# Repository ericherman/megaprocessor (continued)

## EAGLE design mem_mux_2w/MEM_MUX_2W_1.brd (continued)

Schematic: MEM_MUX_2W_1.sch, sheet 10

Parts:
Q61, Q62, Q63, Q64, Q65, Q66, Q67, Q68, Q69, Q70, Q71, Q72, Q73, Q74, Q75, Q76, Q77, Q78, Q79, Q80, Q81, Q82, Q83, Q84: 2N7000; TO92-DGS
R77, R78, R79, R80, R81, R82, R83, R84, R85, R86, R87, R88, R89, R90, R91, R92, R93, R94, R95, R96, R97, R98, R99, R100: 10k; R_P2INCH

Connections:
+5V: R77.2, R78.2, R79.2, R80.2, R81.2, R82.2, R83.2, R84.2, R85.2, R86.2, R87.2, R88.2, R89.2, R90.2, R91.2, R92.2, R93.2, R94.2, R95.2, R96.2, R97.2, R98.2, R99.2, R100.2; also elsewhere on the board
A0_N: Q69.G; also elsewhere on the board
A1_N: Q70.G; also elsewhere on the board
A2_N: Q71.G; also elsewhere on the board
A3_N: Q72.G; also elsewhere on the board
A4_N: Q73.G; also elsewhere on the board
A5_N: Q74.G; also elsewhere on the board
A6_N: Q75.G; also elsewhere on the board
A7_N: Q76.G; also elsewhere on the board
A8_N: Q77.G; also elsewhere on the board
A9_N: Q78.G; also elsewhere on the board
A10_N: Q79.G; also elsewhere on the board
A11_N: Q80.G; also elsewhere on the board
A12_N: Q81.G; also elsewhere on the board
A13_N: Q82.G; also elsewhere on the board
A14_N: Q83.G; also elsewhere on the board
A15_N: Q84.G; also elsewhere on the board
GND: Q61.S, Q62.S, Q63.S, Q64.S, Q65.S, Q66.S, Q67.S, Q68.S, Q69.S, Q70.S, Q71.S, Q72.S, Q73.S, Q74.S, Q75.S, Q76.S, Q77.S, Q78.S, Q79.S, Q80.S, Q81.S, Q82.S, Q83.S, Q84.S; also elsewhere on the board
P1_A0: Q69.D, R85.1; also elsewhere on the board
P1_A1: Q70.D, R86.1; also elsewhere on the board
P1_A2: Q71.D, R87.1; also elsewhere on the board
P1_A3: Q72.D, R88.1; also elsewhere on the board
P1_A4: Q73.D, R89.1; also elsewhere on the board
P1_A5: Q74.D, R90.1; also elsewhere on the board
P1_A6: Q75.D, R91.1; also elsewhere on the board
P1_A7: Q76.D, R92.1; also elsewhere on the board
P1_A8: Q77.D, R93.1; also elsewhere on the board
P1_A9: Q78.D, R94.1; also elsewhere on the board
P1_A10: Q79.D, R95.1; also elsewhere on the board
P1_A11: Q80.D, R96.1; also elsewhere on the board
P1_A12: Q81.D, R97.1; also elsewhere on the board
P1_A13: Q82.D, R98.1; also elsewhere on the board
P1_A14: Q83.D, R99.1; also elsewhere on the board
P1_A15: Q84.D, R100.1; also elsewhere on the board
P1_WD0: Q61.D, R77.1; also elsewhere on the board
P1_WD1: Q62.D, R78.1; also elsewhere on the board
P1_WD2: Q63.D, R79.1; also elsewhere on the board
P1_WD3: Q64.D, R80.1; also elsewhere on the board
P1_WD4: Q65.D, R81.1; also elsewhere on the board
P1_WD5: Q66.D, R82.1; also elsewhere on the board
P1_WD6: Q67.D, R83.1; also elsewhere on the board
P1_WD7: Q68.D, R84.1; also elsewhere on the board
WD0_N: Q61.G; also elsewhere on the board
WD1_N: Q62.G; also elsewhere on the board
WD2_N: Q63.G; also elsewhere on the board
WD3_N: Q64.G; also elsewhere on the board
WD4_N: Q65.G; also elsewhere on the board
WD5_N: Q66.G; also elsewhere on the board
WD6_N: Q67.G; also elsewhere on the board
WD7_N: Q68.G; also elsewhere on the board

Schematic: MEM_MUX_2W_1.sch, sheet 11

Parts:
D33, D34, D35, D69: L-1334SRT; LED3MM
Q169, Q170, Q171, Q174, Q175, Q176, Q179, Q180, Q181, Q184, Q185, Q186: 2N7000; TO92-DGS
R201, R203, R205, R207, R257, R258, R259, R260: 10k; R_P2INCH
R202, R204, R206, R208: 470; R_P2INCH

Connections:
+5V: D33.A, D34.A, D35.A, D69.A, R201.2, R203.2, R205.2, R207.2, R257.2, R258.2, R259.2, R260.2; also elsewhere on the board
GND: Q170.S, Q171.S, Q175.S, Q176.S, Q180.S, Q181.S, Q185.S, Q186.S; also elsewhere on the board
unnamed: Q174.D, Q175.G, R203.1, R204.1
unnamed: D33.K (C), R204.2
unnamed: Q174.S, Q176.D
unnamed: Q179.D, Q180.G, R205.1, R206.1
unnamed: D34.K (C), R206.2
unnamed: Q179.S, Q181.D
unnamed: Q184.D, Q185.G, R207.1, R208.1
unnamed: D35.K (C), R208.2
unnamed: Q184.S, Q186.D
unnamed: Q169.D, Q170.G, R201.1, R202.1
unnamed: D69.K (C), R202.2
unnamed: Q169.S, Q171.D
P0_RD0_B: Q169.G; also elsewhere on the board
P0_RD1_B: Q174.G; also elsewhere on the board
P0_RD2_B: Q179.G; also elsewhere on the board
P0_RD3_B: Q184.G; also elsewhere on the board
P1_RD0_B: Q171.G; also elsewhere on the board
P1_RD1_B: Q176.G; also elsewhere on the board
P1_RD2_B: Q181.G; also elsewhere on the board
P1_RD3_B: Q186.G; also elsewhere on the board
RD0: Q170.D, R257.1; also elsewhere on the board
RD1: Q175.D, R258.1; also elsewhere on the board
RD2: Q180.D, R259.1; also elsewhere on the board
RD3: Q185.D, R260.1; also elsewhere on the board

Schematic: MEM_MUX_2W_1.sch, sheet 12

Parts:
D36, D37, D38, D39: L-1334SRT; LED3MM
Q189, Q190, Q191, Q194, Q195, Q196, Q199, Q200, Q201, Q204, Q205, Q206: 2N7000; TO92-DGS
R209, R211, R213, R215, R253, R254, R255, R256: 10k; R_P2INCH
R210, R212, R214, R216: 470; R_P2INCH

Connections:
+5V: D36.A, D37.A, D38.A, D39.A, R209.2, R211.2, R213.2, R215.2, R253.2, R254.2, R255.2, R256.2; also elsewhere on the board
GND: Q190.S, Q191.S, Q195.S, Q196.S, Q200.S, Q201.S, Q205.S, Q206.S; also elsewhere on the board
unnamed: Q189.D, Q190.G, R209.1, R210.1
unnamed: D36.K (C), R210.2
unnamed: Q189.S, Q191.D
unnamed: Q194.D, Q195.G, R211.1, R212.1
unnamed: D37.K (C), R212.2
unnamed: Q194.S, Q196.D
unnamed: Q199.D, Q200.G, R213.1, R214.1
unnamed: D38.K (C), R214.2
unnamed: Q199.S, Q201.D
unnamed: Q204.D, Q205.G, R215.1, R216.1
unnamed: D39.K (C), R216.2
unnamed: Q204.S, Q206.D
P0_RD4_B: Q189.G; also elsewhere on the board
P0_RD5_B: Q194.G; also elsewhere on the board
P0_RD6_B: Q199.G; also elsewhere on the board
P0_RD7_B: Q204.G; also elsewhere on the board
P1_RD4_B: Q191.G; also elsewhere on the board
P1_RD5_B: Q196.G; also elsewhere on the board
P1_RD6_B: Q201.G; also elsewhere on the board
P1_RD7_B: Q206.G; also elsewhere on the board
RD4: Q190.D, R253.1; also elsewhere on the board
RD5: Q195.D, R254.1; also elsewhere on the board
RD6: Q200.D, R255.1; also elsewhere on the board
RD7: Q205.D, R256.1; also elsewhere on the board

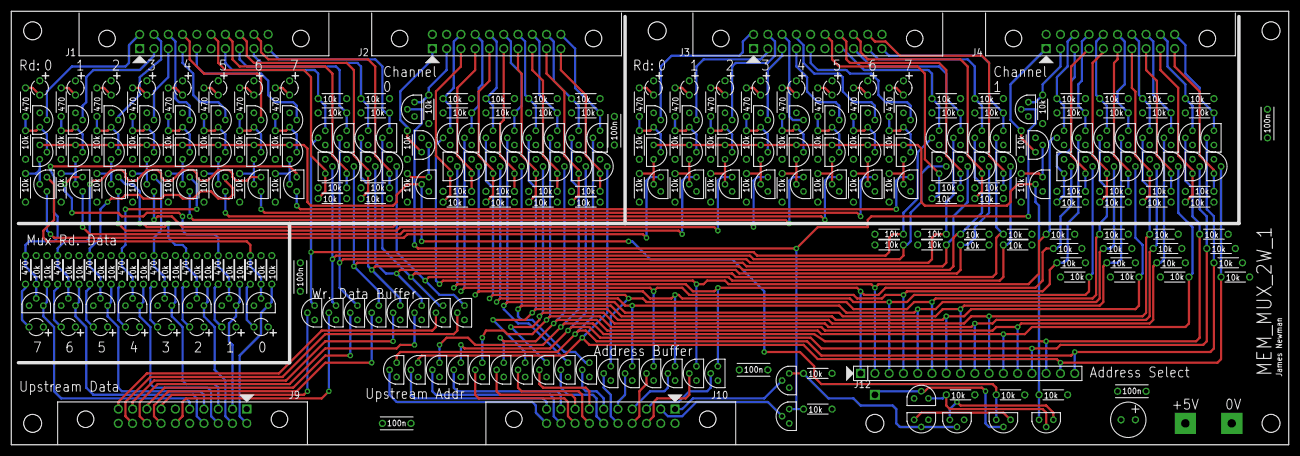
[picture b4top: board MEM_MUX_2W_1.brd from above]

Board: 4 copper layers, 227.3 x 77.1 mm, 343 parts (0 on the bottom side), 210 nets.

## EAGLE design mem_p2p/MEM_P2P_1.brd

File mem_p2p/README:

frame to frame memory connection

This combines the address and data bus into a single cable for
transferring between frames. It includes protection circuitry for
inputs.

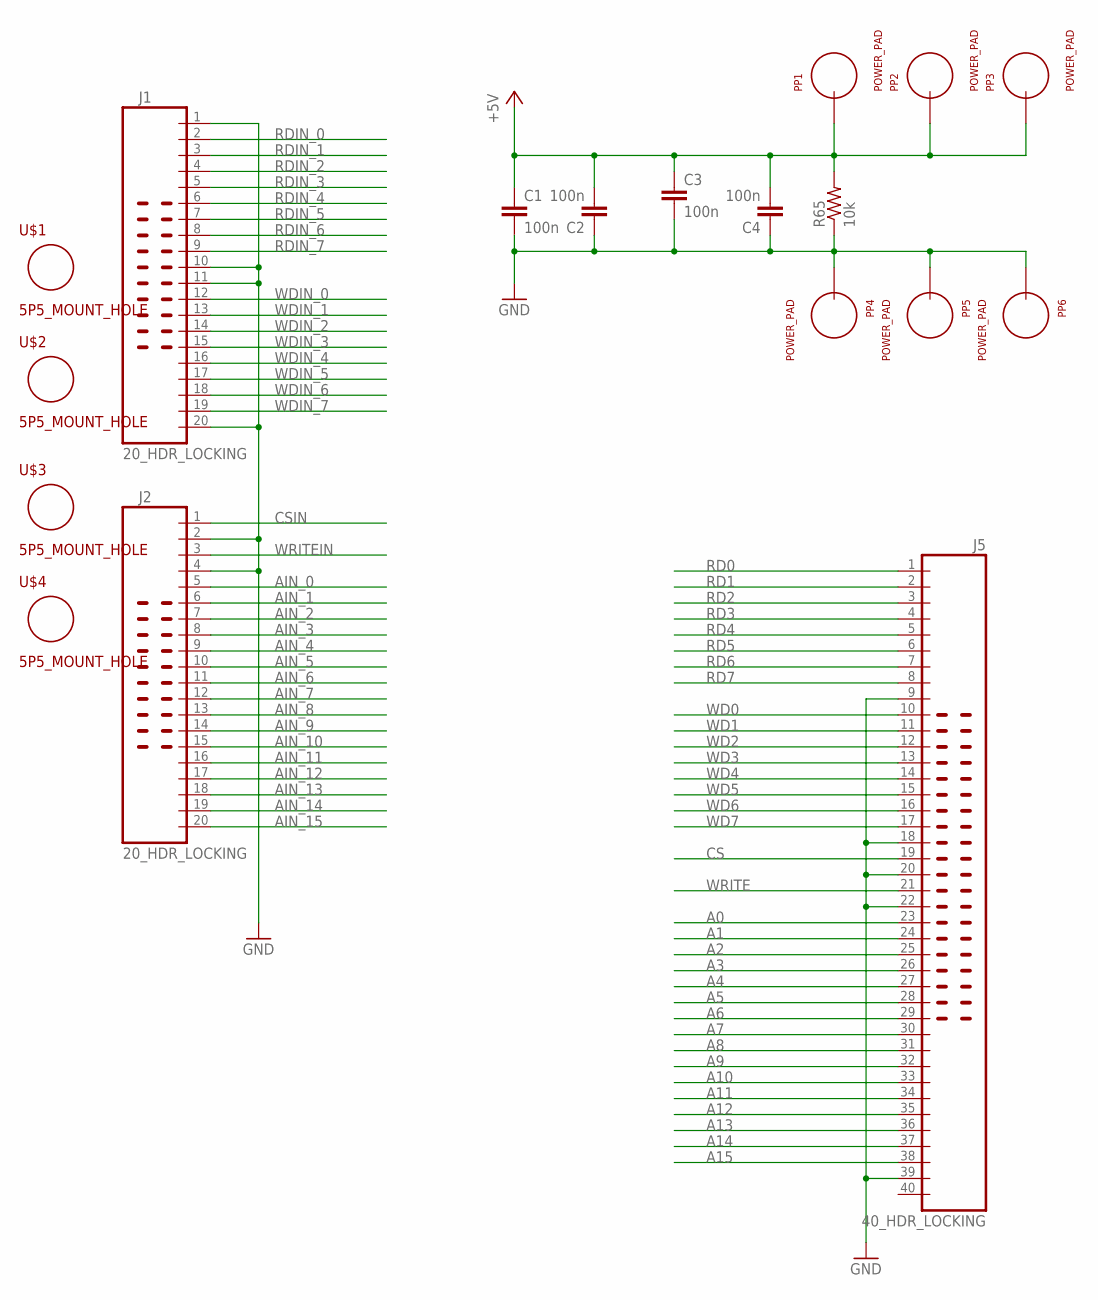
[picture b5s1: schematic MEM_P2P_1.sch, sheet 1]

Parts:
C1, C2, C3, C4: 100n; CAP_P2INCH
J1, J2: 20_HDR_LOCKING
J5: 40_HDR_LOCKING
PP1, PP2, PP3, PP4, PP5, PP6: POWER_PAD
R65: 10k; R_P2INCH
U$1, U$2, U$3, U$4: 5P5_MOUNT_HOLE; 5P5M_HOLE

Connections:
+5V: C1.1, C2.2, C3.1, C4.2, PP1.1, PP2.1, PP3.1, R65.2; also elsewhere on the board
A0: J5.23; also elsewhere on the board
A1: J5.24; also elsewhere on the board
A2: J5.25; also elsewhere on the board
A3: J5.26; also elsewhere on the board
A4: J5.27; also elsewhere on the board
A5: J5.28; also elsewhere on the board
A6: J5.29; also elsewhere on the board
A7: J5.30; also elsewhere on the board
A8: J5.31; also elsewhere on the board
A9: J5.32; also elsewhere on the board
A10: J5.33; also elsewhere on the board
A11: J5.34; also elsewhere on the board
A12: J5.35; also elsewhere on the board
A13: J5.36; also elsewhere on the board
A14: J5.37; also elsewhere on the board
A15: J5.38; also elsewhere on the board
AIN_0: J2.5; also elsewhere on the board
AIN_1: J2.6; also elsewhere on the board
AIN_2: J2.7; also elsewhere on the board
AIN_3: J2.8; also elsewhere on the board
AIN_4: J2.9; also elsewhere on the board
AIN_5: J2.10; also elsewhere on the board
AIN_6: J2.11; also elsewhere on the board
AIN_7: J2.12; also elsewhere on the board
AIN_8: J2.13; also elsewhere on the board
AIN_9: J2.14; also elsewhere on the board
AIN_10: J2.15; also elsewhere on the board
AIN_11: J2.16; also elsewhere on the board
AIN_12: J2.17; also elsewhere on the board
AIN_13: J2.18; also elsewhere on the board
AIN_14: J2.19; also elsewhere on the board
AIN_15: J2.20; also elsewhere on the board
CS: J5.19; also elsewhere on the board
CSIN: J2.1; also elsewhere on the board
GND: C1.2, C2.1, C3.2, C4.1, J1.1, J1.10, J1.11, J1.20, J2.2, J2.4, J5.9, J5.18, J5.20, J5.22, J5.39, PP4.1, PP5.1, PP6.1, R65.1; also elsewhere on the board
RD0: J5.1; also elsewhere on the board
RD1: J5.2; also elsewhere on the board
RD2: J5.3; also elsewhere on the board
RD3: J5.4; also elsewhere on the board
RD4: J5.5; also elsewhere on the board
RD5: J5.6; also elsewhere on the board
RD6: J5.7; also elsewhere on the board
RD7: J5.8; also elsewhere on the board
RDIN_0: J1.2; also elsewhere on the board
RDIN_1: J1.3; also elsewhere on the board
RDIN_2: J1.4; also elsewhere on the board
RDIN_3: J1.5; also elsewhere on the board
RDIN_4: J1.6; also elsewhere on the board
RDIN_5: J1.7; also elsewhere on the board
RDIN_6: J1.8; also elsewhere on the board
RDIN_7: J1.9; also elsewhere on the board
WD0: J5.10; also elsewhere on the board
WD1: J5.11; also elsewhere on the board
WD2: J5.12; also elsewhere on the board
WD3: J5.13; also elsewhere on the board
WD4: J5.14; also elsewhere on the board
WD5: J5.15; also elsewhere on the board
WD6: J5.16; also elsewhere on the board
WD7: J5.17; also elsewhere on the board
WDIN_0: J1.12; also elsewhere on the board
WDIN_1: J1.13; also elsewhere on the board
WDIN_2: J1.14; also elsewhere on the board
WDIN_3: J1.15; also elsewhere on the board
WDIN_4: J1.16; also elsewhere on the board
WDIN_5: J1.17; also elsewhere on the board
WDIN_6: J1.18; also elsewhere on the board
WDIN_7: J1.19; also elsewhere on the board
WRITE: J5.21; also elsewhere on the board
WRITEIN: J2.3; also elsewhere on the board

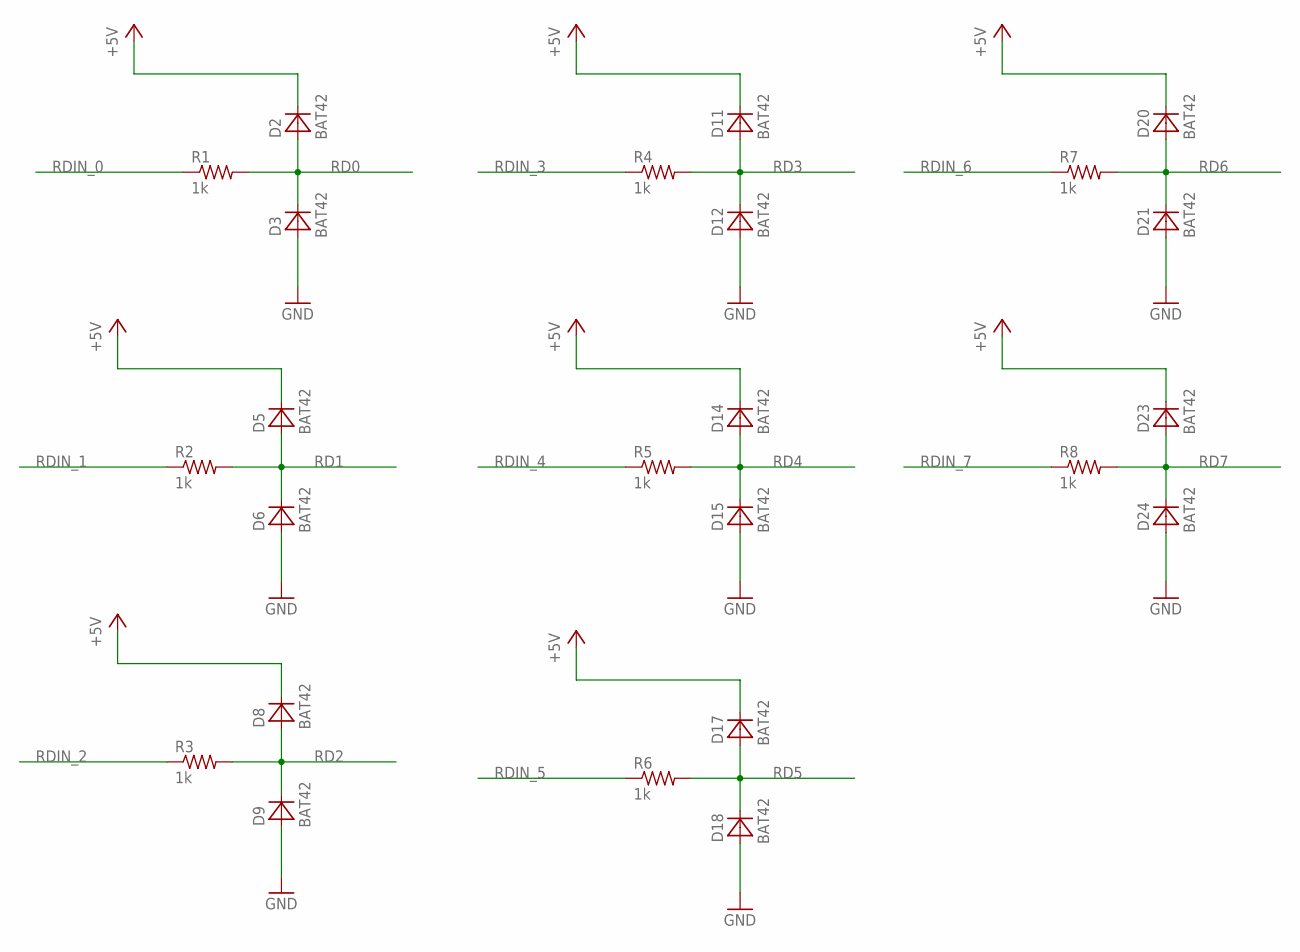
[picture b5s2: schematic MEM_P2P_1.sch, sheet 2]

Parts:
D2, D3, D5, D6, D8, D9, D11, D12, D14, D15, D17, D18, D20, D21, D23, D24: BAT42; DO34-5
R1, R2, R3, R4, R5, R6, R7, R8: 1k; R_P2INCH

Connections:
+5V: D2.C, D5.C, D8.C, D11.C, D14.C, D17.C, D20.C, D23.C; also elsewhere on the board
GND: D3.A, D6.A, D9.A, D12.A, D15.A, D18.A, D21.A, D24.A; also elsewhere on the board
RD0: D2.A, D3.C, R1.2; also elsewhere on the board
RD1: D5.A, D6.C, R2.2; also elsewhere on the board
RD2: D8.A, D9.C, R3.2; also elsewhere on the board
RD3: D11.A, D12.C, R4.2; also elsewhere on the board
RD4: D14.A, D15.C, R5.2; also elsewhere on the board
RD5: D17.A, D18.C, R6.2; also elsewhere on the board
RD6: D20.A, D21.C, R7.2; also elsewhere on the board
RD7: D23.A, D24.C, R8.2; also elsewhere on the board
RDIN_0: R1.1; also elsewhere on the board
RDIN_1: R2.1; also elsewhere on the board
RDIN_2: R3.1; also elsewhere on the board
RDIN_3: R4.1; also elsewhere on the board
RDIN_4: R5.1; also elsewhere on the board
RDIN_5: R6.1; also elsewhere on the board
RDIN_6: R7.1; also elsewhere on the board
RDIN_7: R8.1; also elsewhere on the board

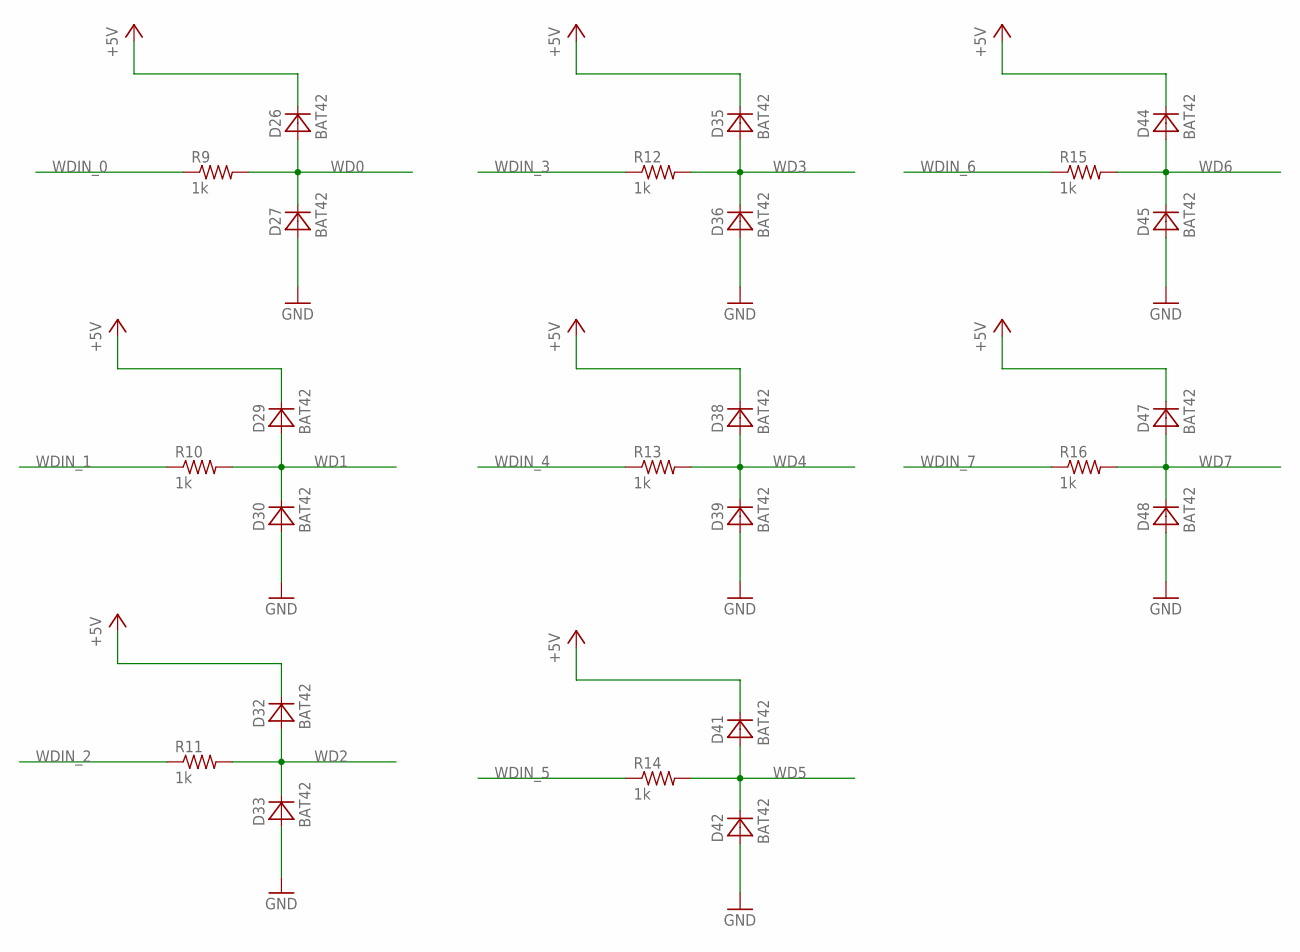
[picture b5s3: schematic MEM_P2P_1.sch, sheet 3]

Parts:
D26, D27, D29, D30, D32, D33, D35, D36, D38, D39, D41, D42, D44, D45, D47, D48: BAT42; DO34-5
R9, R10, R11, R12, R13, R14, R15, R16: 1k; R_P2INCH

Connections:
+5V: D26.C, D29.C, D32.C, D35.C, D38.C, D41.C, D44.C, D47.C; also elsewhere on the board
GND: D27.A, D30.A, D33.A, D36.A, D39.A, D42.A, D45.A, D48.A; also elsewhere on the board
WD0: D26.A, D27.C, R9.2; also elsewhere on the board
WD1: D29.A, D30.C, R10.2; also elsewhere on the board
WD2: D32.A, D33.C, R11.2; also elsewhere on the board
WD3: D35.A, D36.C, R12.2; also elsewhere on the board
WD4: D38.A, D39.C, R13.2; also elsewhere on the board
WD5: D41.A, D42.C, R14.2; also elsewhere on the board
WD6: D44.A, D45.C, R15.2; also elsewhere on the board
WD7: D47.A, D48.C, R16.2; also elsewhere on the board
WDIN_0: R9.1; also elsewhere on the board
WDIN_1: R10.1; also elsewhere on the board
WDIN_2: R11.1; also elsewhere on the board
WDIN_3: R12.1; also elsewhere on the board
WDIN_4: R13.1; also elsewhere on the board
WDIN_5: R14.1; also elsewhere on the board
WDIN_6: R15.1; also elsewhere on the board
WDIN_7: R16.1; also elsewhere on the board

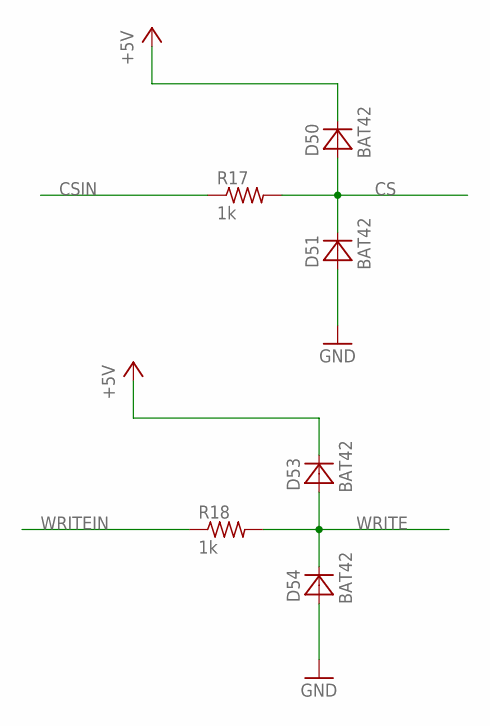
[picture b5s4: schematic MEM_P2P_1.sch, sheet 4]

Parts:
D50, D51, D53, D54: BAT42; DO34-5
R17, R18: 1k; R_P2INCH

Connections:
+5V: D50.C, D53.C; also elsewhere on the board
CS: D50.A, D51.C, R17.2; also elsewhere on the board
CSIN: R17.1; also elsewhere on the board
GND: D51.A, D54.A; also elsewhere on the board
WRITE: D53.A, D54.C, R18.2; also elsewhere on the board
WRITEIN: R18.1; also elsewhere on the board

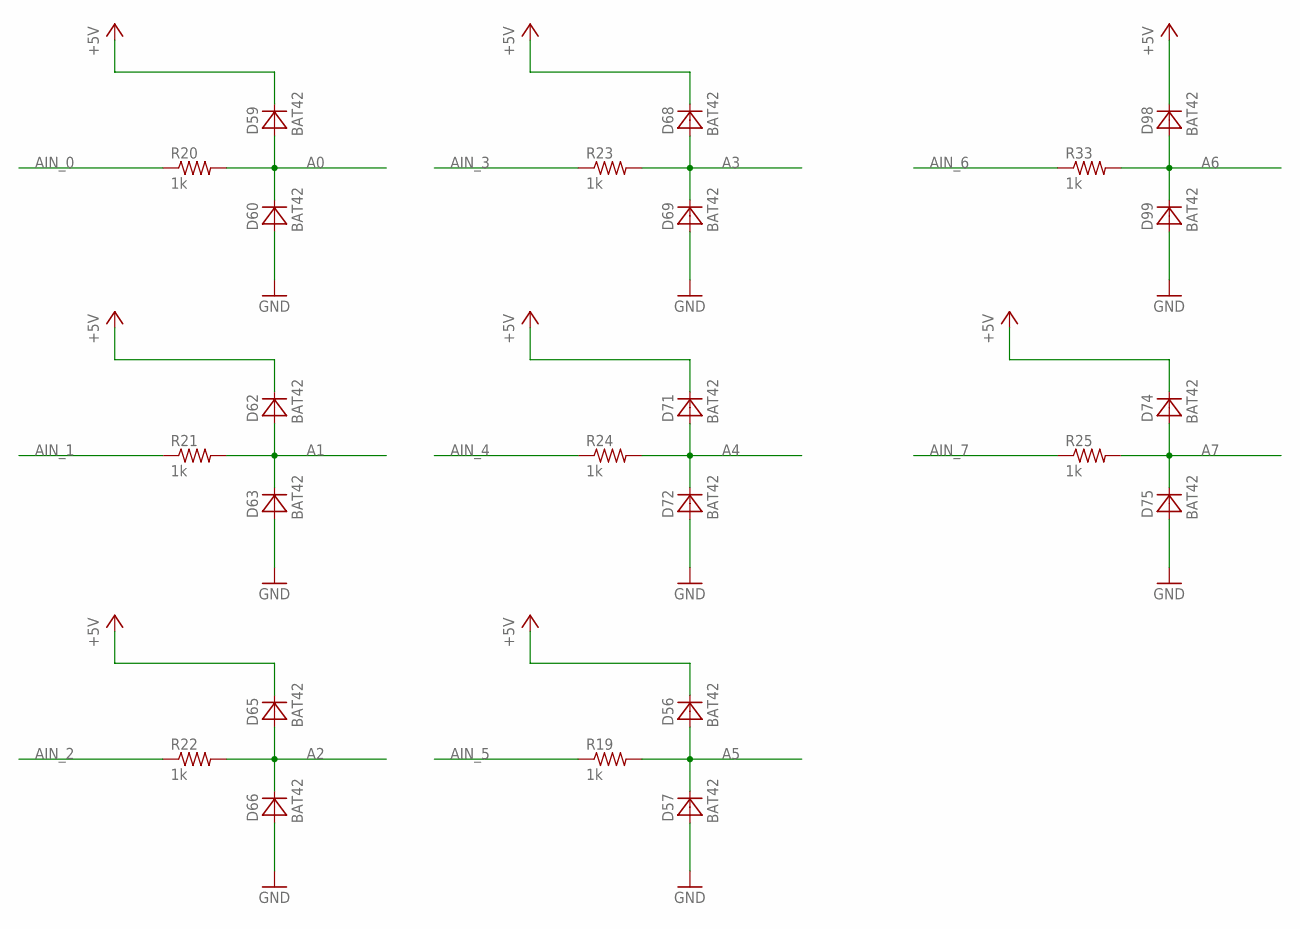
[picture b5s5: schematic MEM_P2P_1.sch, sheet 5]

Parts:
D56, D57, D59, D60, D62, D63, D65, D66, D68, D69, D71, D72, D74, D75, D98, D99: BAT42; DO34-5
R19, R20, R21, R22, R23, R24, R25, R33: 1k; R_P2INCH

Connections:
+5V: D56.C, D59.C, D62.C, D65.C, D68.C, D71.C, D74.C, D98.C; also elsewhere on the board
A0: D59.A, D60.C, R20.2; also elsewhere on the board
A1: D62.A, D63.C, R21.2; also elsewhere on the board
A2: D65.A, D66.C, R22.2; also elsewhere on the board
A3: D68.A, D69.C, R23.2; also elsewhere on the board
A4: D71.A, D72.C, R24.2; also elsewhere on the board
A5: D56.A, D57.C, R19.2; also elsewhere on the board
A6: D98.A, D99.C, R33.2; also elsewhere on the board
A7: D74.A, D75.C, R25.2; also elsewhere on the board
AIN_0: R20.1; also elsewhere on the board
AIN_1: R21.1; also elsewhere on the board
AIN_2: R22.1; also elsewhere on the board
AIN_3: R23.1; also elsewhere on the board
AIN_4: R24.1; also elsewhere on the board
AIN_5: R19.1; also elsewhere on the board
AIN_6: R33.1; also elsewhere on the board
AIN_7: R25.1; also elsewhere on the board
GND: D57.A, D60.A, D63.A, D66.A, D69.A, D72.A, D75.A, D99.A; also elsewhere on the board

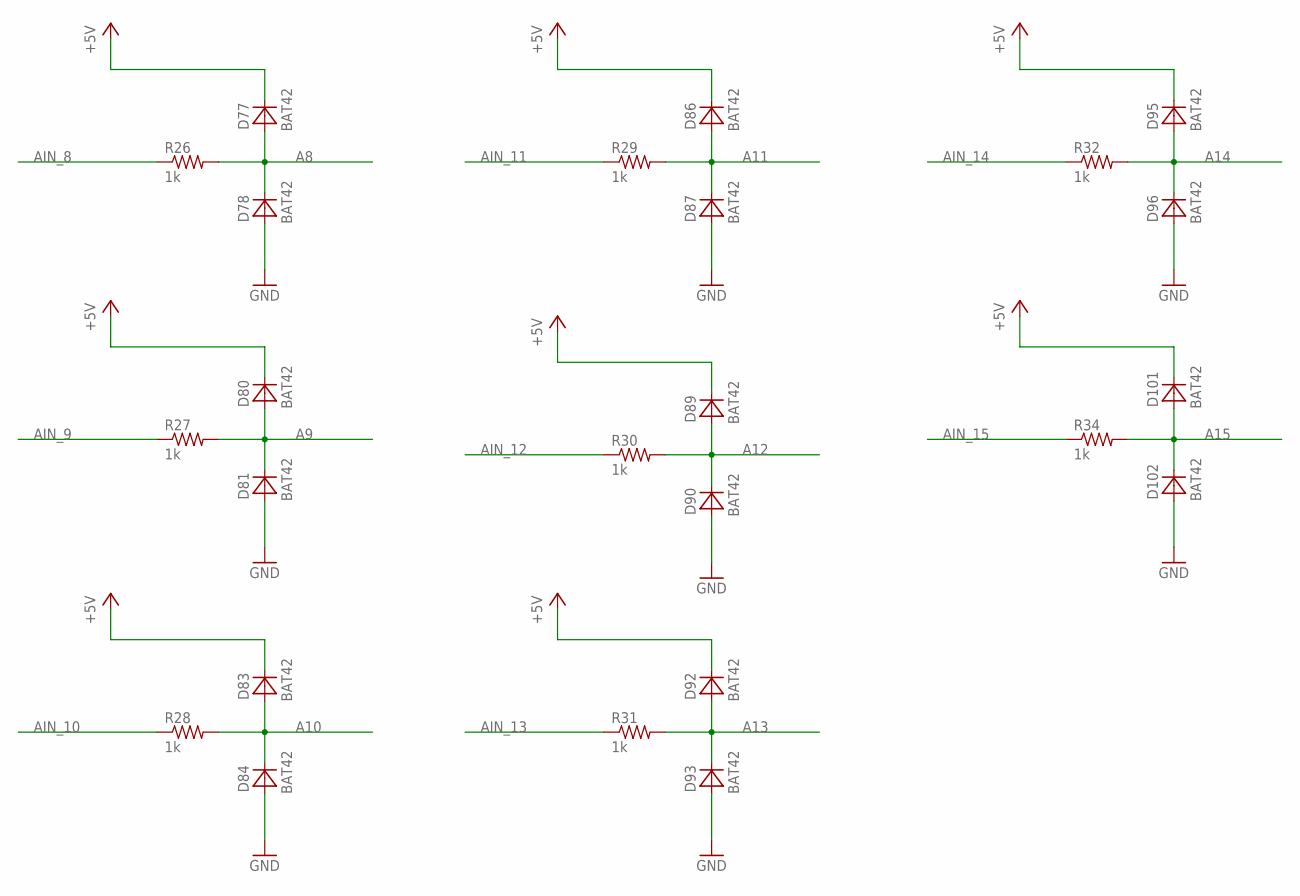
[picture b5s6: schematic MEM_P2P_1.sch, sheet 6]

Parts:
D77, D78, D80, D81, D83, D84, D86, D87, D89, D90, D92, D93, D95, D96, D101, D102: BAT42; DO34-5
R26, R27, R28, R29, R30, R31, R32, R34: 1k; R_P2INCH

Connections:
+5V: D77.C, D80.C, D83.C, D86.C, D89.C, D92.C, D95.C, D101.C; also elsewhere on the board
A8: D77.A, D78.C, R26.2; also elsewhere on the board
A9: D80.A, D81.C, R27.2; also elsewhere on the board
A10: D83.A, D84.C, R28.2; also elsewhere on the board
A11: D86.A, D87.C, R29.2; also elsewhere on the board
A12: D89.A, D90.C, R30.2; also elsewhere on the board
A13: D92.A, D93.C, R31.2; also elsewhere on the board
A14: D95.A, D96.C, R32.2; also elsewhere on the board
A15: D101.A, D102.C, R34.2; also elsewhere on the board
AIN_8: R26.1; also elsewhere on the board
AIN_9: R27.1; also elsewhere on the board
AIN_10: R28.1; also elsewhere on the board
AIN_11: R29.1; also elsewhere on the board
AIN_12: R30.1; also elsewhere on the board
AIN_13: R31.1; also elsewhere on the board
AIN_14: R32.1; also elsewhere on the board
AIN_15: R34.1; also elsewhere on the board
GND: D78.A, D81.A, D84.A, D87.A, D90.A, D93.A, D96.A, D102.A; also elsewhere on the board

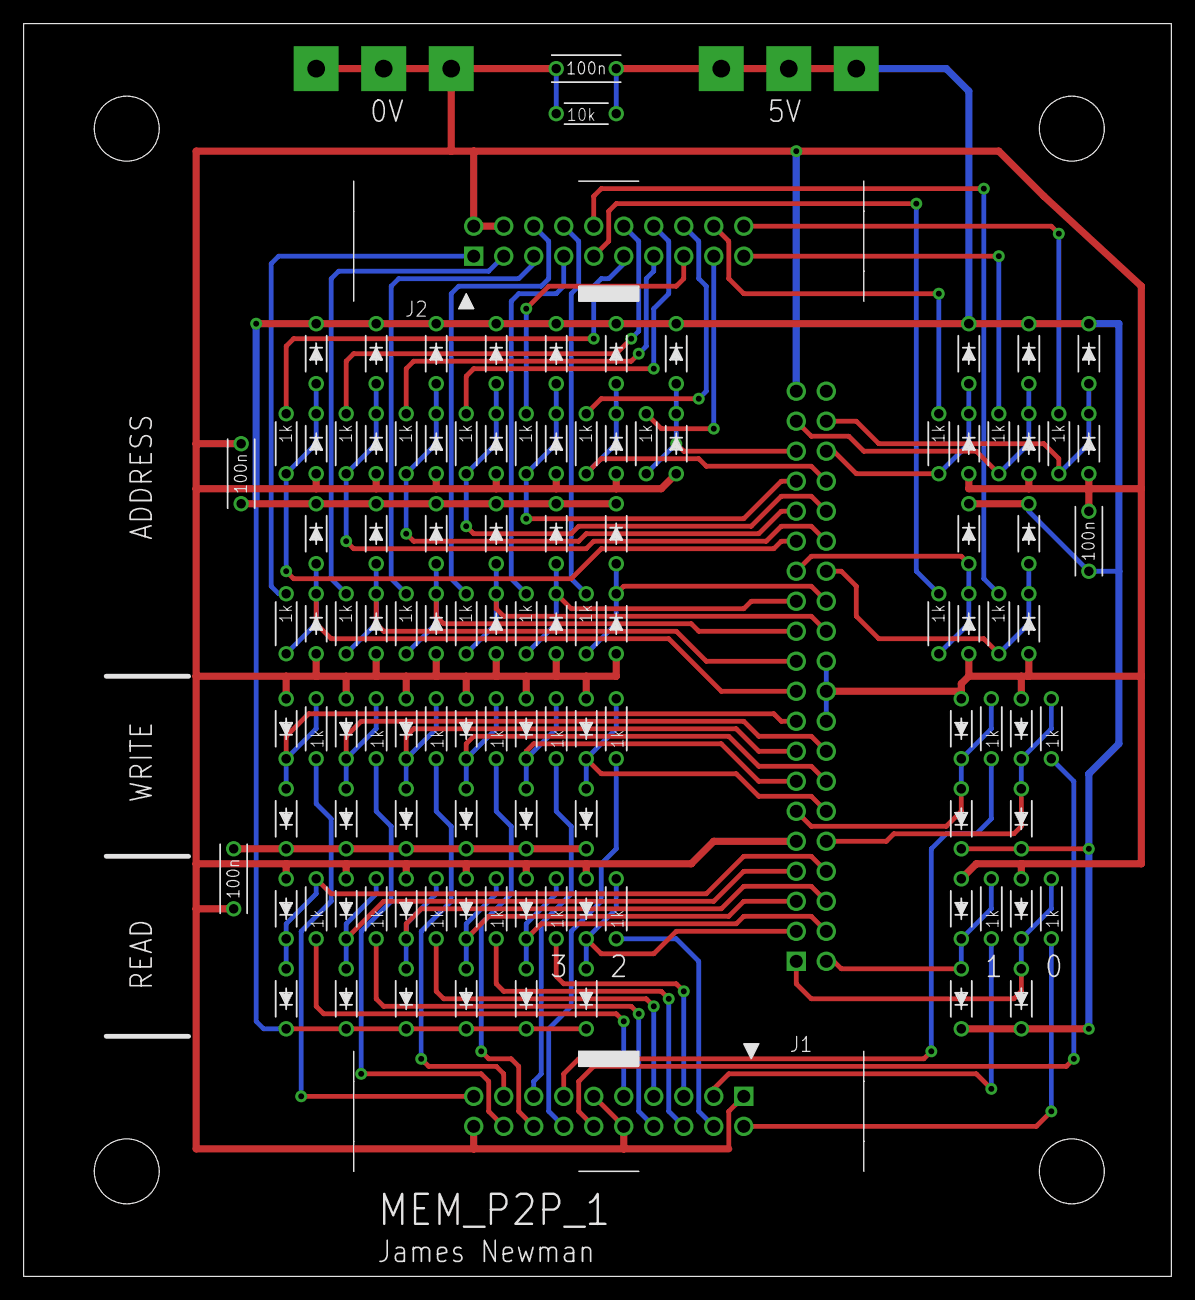
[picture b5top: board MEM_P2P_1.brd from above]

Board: 2 copper layers, 97.2 x 106.0 mm, 120 parts (1 on the bottom side), 70 nets.

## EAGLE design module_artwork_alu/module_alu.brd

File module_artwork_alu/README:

ALU

This is where the arithmetic and logical operations are carried out. It
splits into two parts ALU1 and ADDER2. Each have two inputs, X and Y.

ADDER2 is much the simpler consisting only of a 16 bit adder/subtractor.

ALU1 has several computational units, a 16 bit adder/subtractor, 16 bit
logic, left and right shifters, logic for the BIT operations. The result
from only one of these is output. Flags reporting various aspects of the
results (zero, negative, overflow)  are sent to the Status Flags
Calculation module.

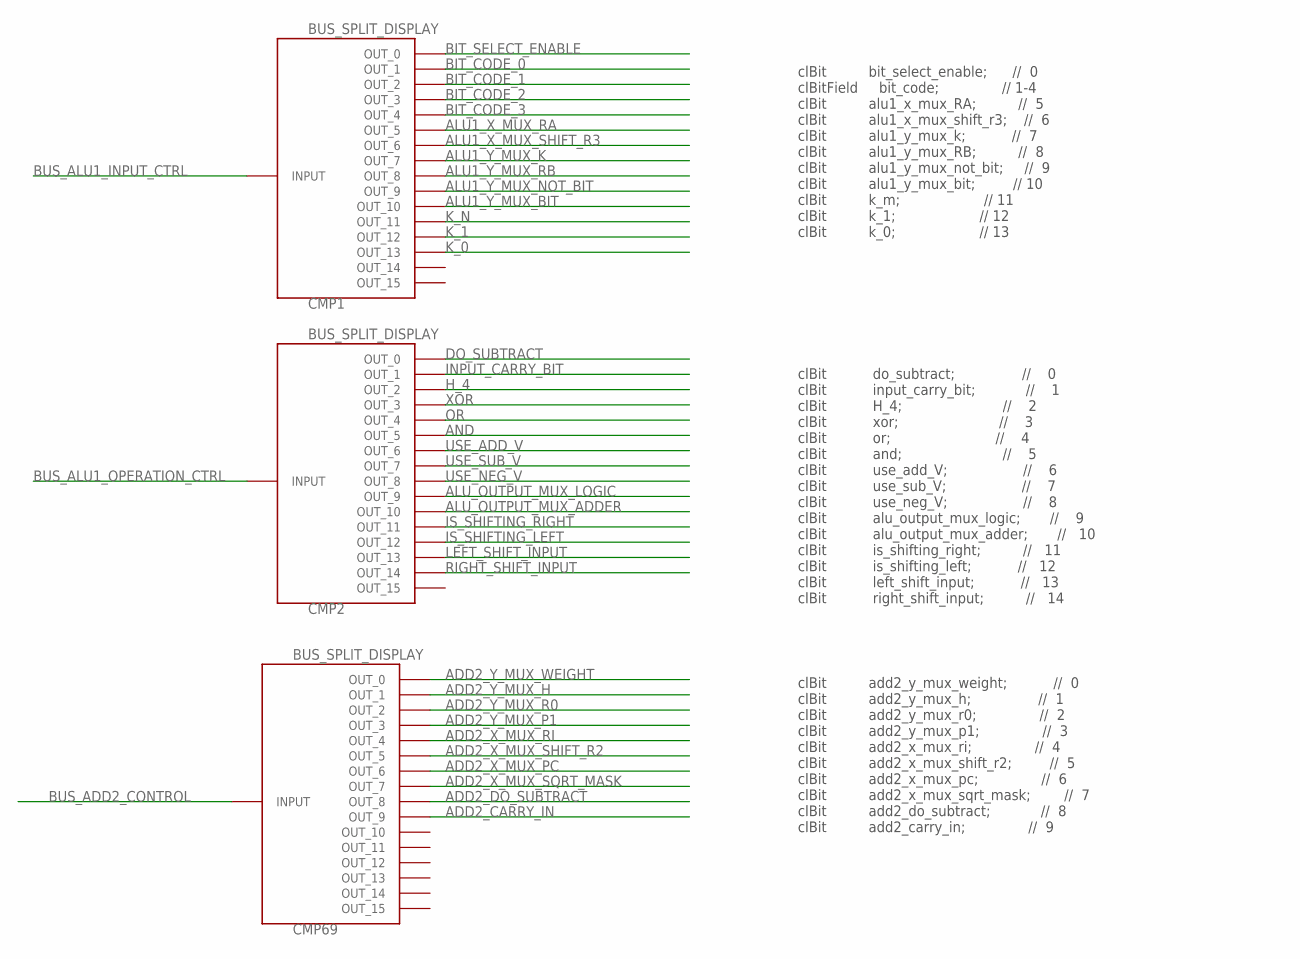
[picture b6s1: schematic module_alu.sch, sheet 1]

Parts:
CMP1, CMP2, CMP69: BUS_SPLIT_DISPLAY

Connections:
ADD2_CARRY_IN: CMP69.P$10 (OUT_9); also elsewhere on the board
ADD2_DO_SUBTRACT: CMP69.P$9 (OUT_8); also elsewhere on the board
ADD2_X_MUX_PC: CMP69.P$7 (OUT_6); also elsewhere on the board
ADD2_X_MUX_RI: CMP69.P$5 (OUT_4); also elsewhere on the board
ADD2_X_MUX_SHIFT_R2: CMP69.P$6 (OUT_5); also elsewhere on the board
ADD2_X_MUX_SQRT_MASK: CMP69.P$8 (OUT_7); also elsewhere on the board
ADD2_Y_MUX_H: CMP69.P$2 (OUT_1); also elsewhere on the board
ADD2_Y_MUX_P1: CMP69.P$4 (OUT_3); also elsewhere on the board
ADD2_Y_MUX_R0: CMP69.P$3 (OUT_2); also elsewhere on the board
ADD2_Y_MUX_WEIGHT: CMP69.P$1 (OUT_0); also elsewhere on the board
ALU1_X_MUX_RA: CMP1.P$6 (OUT_5); also elsewhere on the board
ALU1_X_MUX_SHIFT_R3: CMP1.P$7 (OUT_6); also elsewhere on the board
ALU1_Y_MUX_BIT: CMP1.P$11 (OUT_10); also elsewhere on the board
ALU1_Y_MUX_K: CMP1.P$8 (OUT_7); also elsewhere on the board
ALU1_Y_MUX_NOT_BIT: CMP1.P$10 (OUT_9); also elsewhere on the board
ALU1_Y_MUX_RB: CMP1.P$9 (OUT_8); also elsewhere on the board
ALU_OUTPUT_MUX_ADDER: CMP2.P$11 (OUT_10); also elsewhere on the board
ALU_OUTPUT_MUX_LOGIC: CMP2.P$10 (OUT_9); also elsewhere on the board
AND: CMP2.P$6 (OUT_5); also elsewhere on the board
BIT_CODE_0: CMP1.P$2 (OUT_1); also elsewhere on the board
BIT_CODE_1: CMP1.P$3 (OUT_2); also elsewhere on the board
BIT_CODE_2: CMP1.P$4 (OUT_3); also elsewhere on the board
BIT_CODE_3: CMP1.P$5 (OUT_4); also elsewhere on the board
BIT_SELECT_ENABLE: CMP1.P$1 (OUT_0); also elsewhere on the board
BUS_ADD2_CONTROL: CMP69.INPUT
BUS_ALU1_INPUT_CTRL: CMP1.INPUT
BUS_ALU1_OPERATION_CTRL: CMP2.INPUT
DO_SUBTRACT: CMP2.P$1 (OUT_0); also elsewhere on the board
H_4: CMP2.P$3 (OUT_2); also elsewhere on the board
INPUT_CARRY_BIT: CMP2.P$2 (OUT_1); also elsewhere on the board
IS_SHIFTING_LEFT: CMP2.P$13 (OUT_12); also elsewhere on the board
IS_SHIFTING_RIGHT: CMP2.P$12 (OUT_11); also elsewhere on the board
K_0: CMP1.P$14 (OUT_13); also elsewhere on the board
K_1: CMP1.P$13 (OUT_12); also elsewhere on the board
K_N: CMP1.P$12 (OUT_11); also elsewhere on the board
LEFT_SHIFT_INPUT: CMP2.P$14 (OUT_13); also elsewhere on the board
OR: CMP2.P$5 (OUT_4); also elsewhere on the board
RIGHT_SHIFT_INPUT: CMP2.P$15 (OUT_14); also elsewhere on the board
USE_ADD_V: CMP2.P$7 (OUT_6); also elsewhere on the board
USE_NEG_V: CMP2.P$9 (OUT_8); also elsewhere on the board
USE_SUB_V: CMP2.P$8 (OUT_7); also elsewhere on the board
XOR: CMP2.P$4 (OUT_3); also elsewhere on the board

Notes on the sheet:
clBit bit_select_enable; // 0 clBitField bit_code; // 1-4 clBit alu1_x_mux_RA; // 5 clBit alu1_x_mux_shift_r3; // 6 clBit alu1_y_mux_k; // 7 clBit alu1_y_mux_RB; // 8 clBit alu1_y_mux_not_bit; // 9 clBit alu1_y_mux_bit; // 10 clBit k_m; // 11 clBit k_1; // 12 clBit k_0; // 13
clBit do_subtract; // 0 clBit input_carry_bit; // 1 clBit H_4; // 2 clBit xor; // 3 clBit or; // 4 clBit and; // 5 clBit use_add_V; // 6 clBit use_sub_V; // 7 clBit use_neg_V; // 8 clBit alu_output_mux_logic; // 9 clBit alu_output_mux_adder; // 10 clBit is_shifting_right; // 11 clBit is_shifting_le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
clBit add2_y_mux_weight; // 0 clBit add2_y_mux_h; // 1 clBit add2_y_mux_r0; // 2 clBit add2_y_mux_p1; // 3 clBit add2_x_mux_ri; // 4 clBit add2_x_mux_shift_r2; // 5 clBit add2_x_mux_pc; // 6 clBit add2_x_mux_sqrt_mask; // 7 clBit add2_do_subtract; // 8 clBit add2_carry_in; // 9
